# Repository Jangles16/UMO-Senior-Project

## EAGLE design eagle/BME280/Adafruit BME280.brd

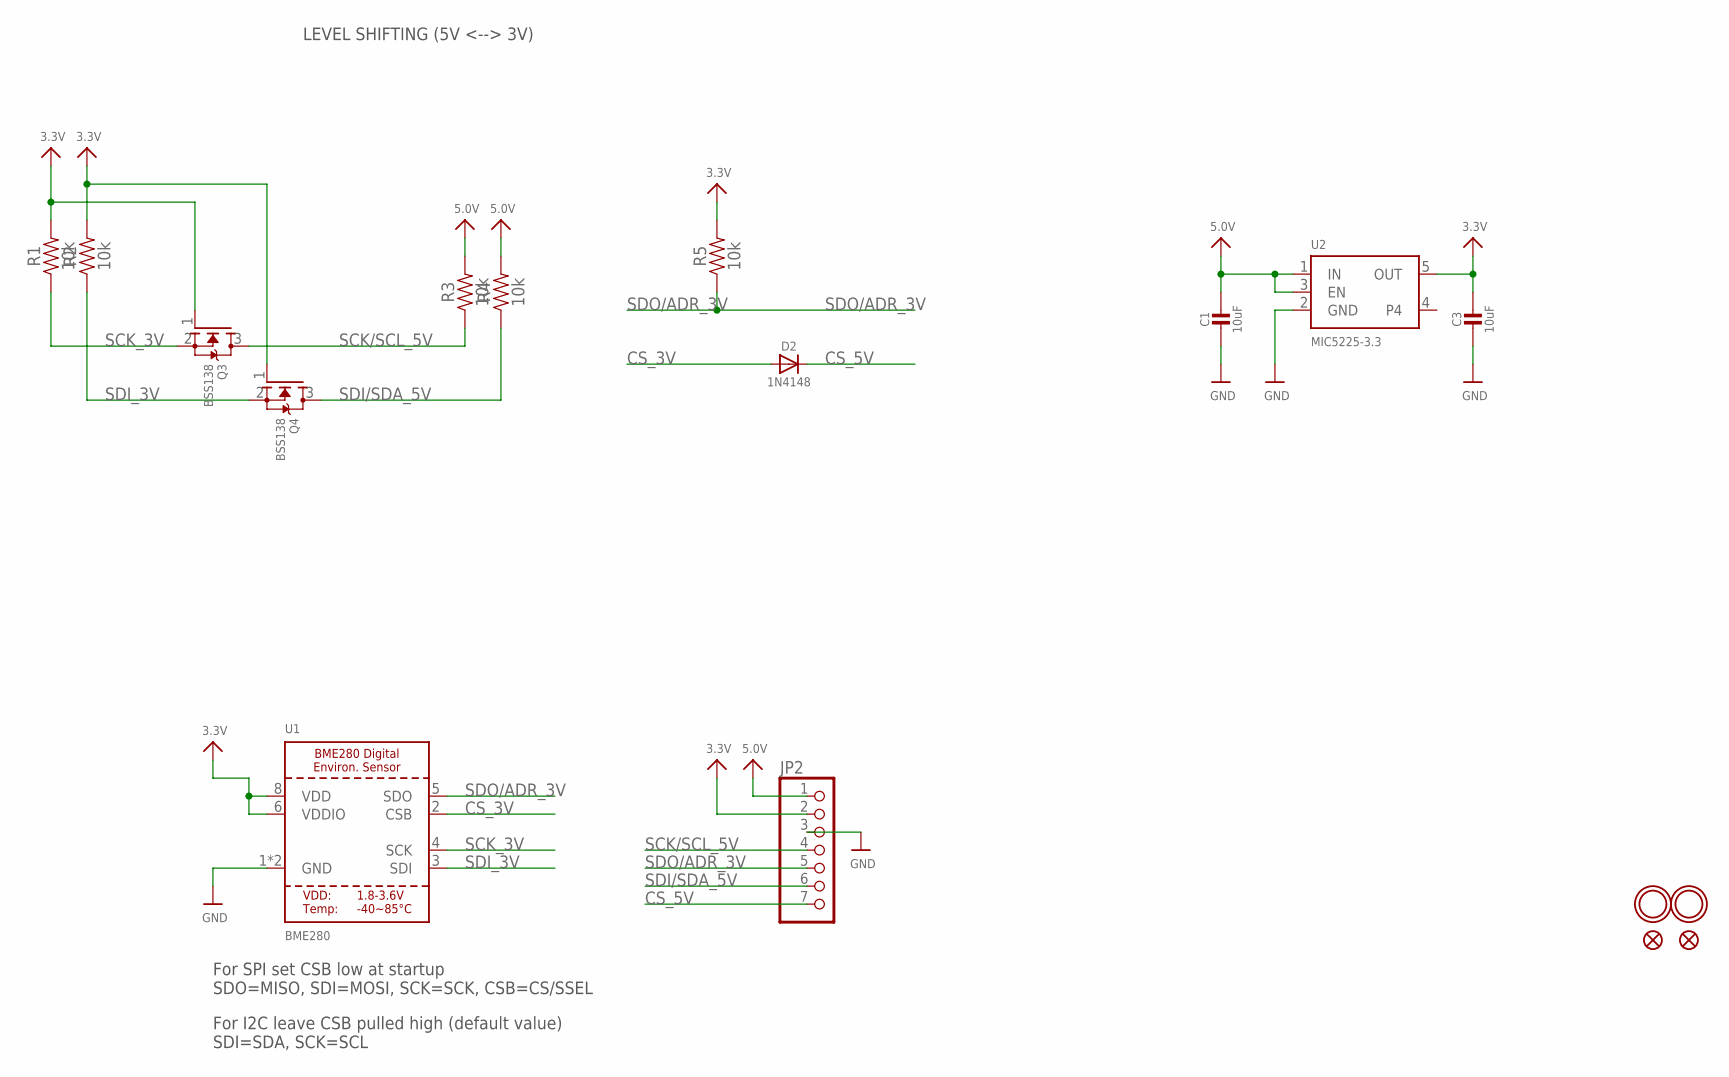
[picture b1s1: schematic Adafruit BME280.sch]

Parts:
C1, C3: 10uF; 0805-NO
D2: 1N4148; SOD-323
JP2: HEADER-1X770MIL; 1X07_ROUND_70
Q3, Q4: BSS138; SOT23-WIDE
R1, R2, R3, R4, R5: 10k; 0603
U1: BME280
U2: MIC5225-3.3; SOT23-5
U$5, U$15: FIDUCIAL""; FIDUCIAL_1MM
U$7, U$8: MOUNTINGHOLE2.0; MOUNTINGHOLE_2.0_PLATED

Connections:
3.3V: C3.1, JP2.2, Q3.1 (G), Q4.1 (G), R1.2, R2.2, R5.2, U1.6 (VDDIO), U1.8 (VDD), U2.5 (OUT)
5.0V: C1.1, JP2.1, R3.2, R4.2, U2.1 (IN), U2.3 (EN)
CS_3V: D2.A, U1.2 (CSB)
CS_5V: D2.C, JP2.7
GND: C1.2, C3.2, JP2.3, U1.1 (GND), U1.7 (GND), U2.2 (GND)
SCK/SCL_5V: JP2.4, Q3.3 (D), R3.1
SCK_3V: Q3.2 (S), R1.1, U1.4 (SCK)
SDI/SDA_5V: JP2.6, Q4.3 (D), R4.1
SDI_3V: Q4.2 (S), R2.1, U1.3 (SDI)
SDO/ADR_3V: JP2.5, R5.1, U1.5 (SDO)

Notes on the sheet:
For SPI set CSB low at startup SDO=MISO, SDI=MOSI, SCK=SCK, CSB=CS/SSEL
For I2C leave CSB pulled high (default value) SDI=SDA, SCK=SCL
LEVEL SHIFTING (5V <--> 3V)

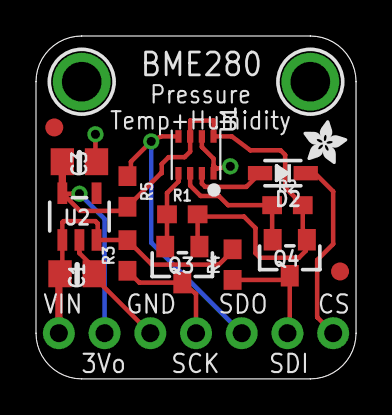
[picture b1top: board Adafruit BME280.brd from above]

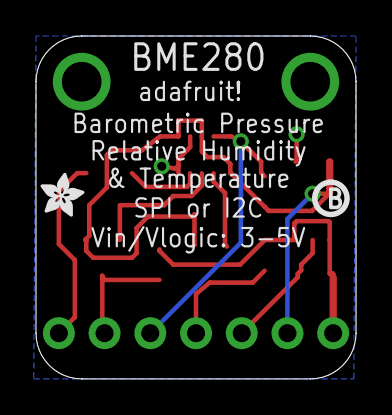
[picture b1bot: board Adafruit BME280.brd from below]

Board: 2 copper layers, 17.8 x 19.1 mm, 20 parts (2 on the bottom side), 10 nets.

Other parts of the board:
U$2, U$6: ADAFRUIT_2.5MM
U$20: PCBFEAT-REV-040

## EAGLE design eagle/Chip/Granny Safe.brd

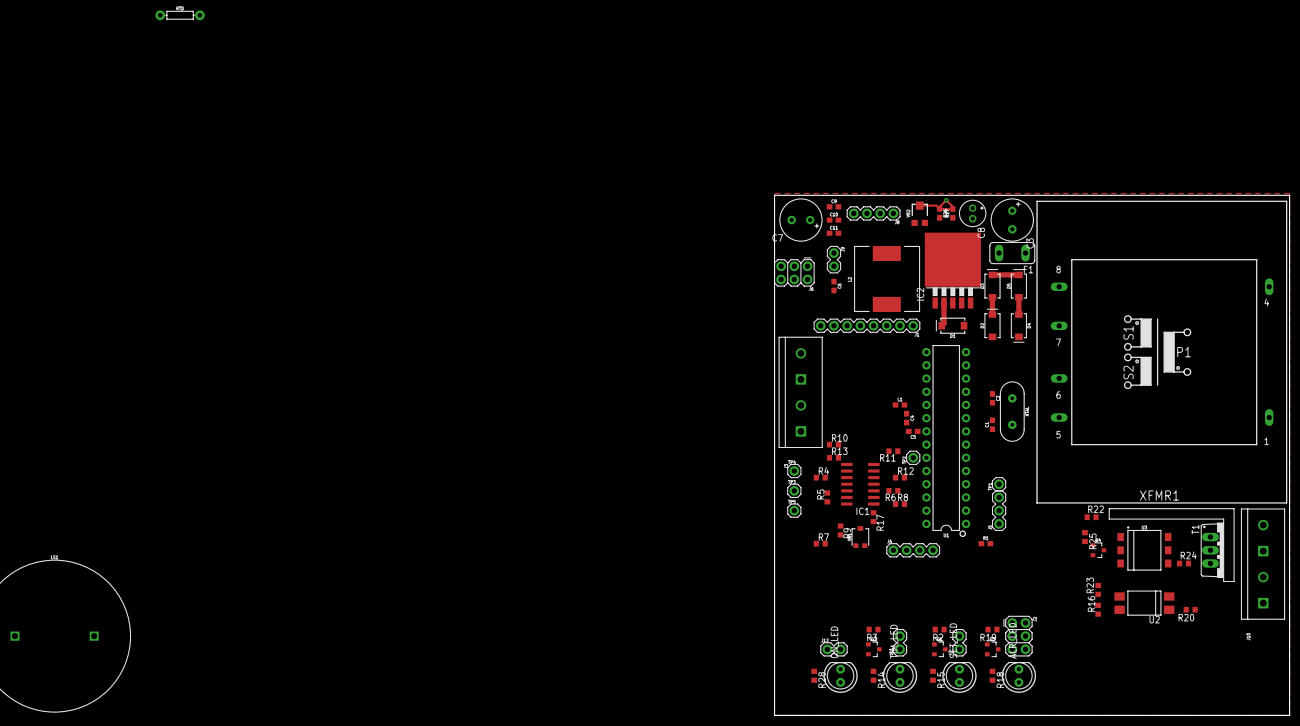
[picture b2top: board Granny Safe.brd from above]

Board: 2 copper layers, 99.0 x 100.0 mm, 87 parts (0 on the bottom side), 59 nets.

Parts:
ALR_LED: LED5MM
C1, C2: 22pF; 0603
C3, C7: 470u; E3,5-8
C4, C5, C6, C9: 0.1uF; 0603
C8: 100u; E2-5
C10: 100pF; 0603
C11: 1nF; 0603
D1, D2, D3, D4, D5: SMA-DIODE
F1: 1.5A; TE5
H1, H2, H3, H4: STAND-OFF
IC1: MCP604SL; SO14
IC2: LM2596S; TO263-5
J1: 3x4 Keypad; 1X08
J2, J6: FEMALE 2x3; 2X3
J3, J10: SCREW-4; SCREWTERMINAL-5MM-2
J4: i2c_16x2; 1X04
J5: 1X03
J7, J11, J12: 1X02
J8: RES JUMPER; 1X04
J9: CKT PWR CONN; 1X02
L1: 10uH; 0603
L2: INDUCTOR; CR75
LS1: SPEAKER; PCB_MOUNT_SPEAKER
ON_LED: LED5MM
Q1, Q2, Q3: SOT23-3
Q4: 2N3904; SOT23-3
R1: 10k; 0603
R2, R3, R19, R25: 2k; R0603
R4, R5: 2.4k; R0603
R6: 100; R0603
R7, R20, R23: 10k; R0603
R8, R9: 20k; R0603
R10, R11: 15k; R0603
R12, R13: 3k; R0603
R14, R15, R18, R28: 150; R0603
R16: 1M; R0603
R17: 5k; R0603
R22: 220; R0603
R24: 180; R0603
R26: 3.3k; 0603
R27: 1k; 0603
RTD: AXIAL-0.3
SET_LED: LED5MM
T1: BT137; TO220BV
TIM_LED: LED5MM
TP1, TP2, TP3, TP4, TP5: 1X01
U1: 328P; DIP28
U2: SFH6206; DIL4-SMD
U3: MOC3051; DIP8SMD
VR1: 10k; TRIMPOT-SMD-3MM-CLOSED
VR2: 10k; TRIMPOT-SMD-TC33X
XFMR1: EE20-2
XTAL: 16MHz; HC49US

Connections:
5V: C6.1, IC1.4, IC1.12, J4.1, J6.1, J6.3, J6.5, J9.2, L1.1, R1.2, R4.2, R5.2, R14.2, R15.2, R18.2, R22.1, R23.2, R28.2, TP4.1, U1.7
ADC0: IC1.7, R11.2, TP2.1, U1.23
ALR: R19.1, U1.18
GATE: R25.1, U1.5
GND: C1.1, C2.1, C3.-, C4.2, C5.2, C6.2, C7.-, C8.-, C9.2, C10.2, C11.2, D1.A, D2.A, D4.C, IC1.11, IC1.13, IC2.3, IC2.5, J3.1, J3.2, J4.2, J6.2, J6.4, J6.6, J8.4, J12.2, ON_LED.K, Q1.2, Q2.2, Q3.2, Q4.2, R6.1, R10.1, R16.1, R27.1, TP3.1, TP5.1, U1.8, U1.22, U2.3, VR2.3
LINE: J10.4, R20.1, T1.T2, U3.6, XFMR1.1
unnamed: C1.2, U1.9, XTAL.2
unnamed: C2.2, U1.10, XTAL.1
unnamed: J1.7, U1.17
unnamed: C5.1, U1.21
unnamed: J1.6, U1.16
unnamed: J1.5, U1.15
unnamed: J1.4, U1.14
unnamed: J1.3, U1.13
unnamed: J1.2, U1.12
unnamed: J1.1, U1.11
unnamed: Q1.1, R2.2
unnamed: IC1.10, J3.3, J3.4, R4.1
unnamed: Q2.1, R3.2
unnamed: IC1.3, R5.1, R6.2
unnamed: IC1.1, R8.2, R12.1
unnamed: J7.1, R15.1, SET_LED.A
unnamed: J11.1, R14.1, TIM_LED.A
unnamed: J11.2, Q2.3, TIM_LED.K
unnamed: J7.2, Q1.3, SET_LED.K
unnamed: R17.2, VR1.2, VR1.3
unnamed: D2.C, D3.A, F1.2
unnamed: ALR_LED.K, J2.1, J2.3, J2.5, Q3.3
unnamed: IC1.2, R7.2, R8.1, R17.1
unnamed: IC1.8, R9.1, R13.1
unnamed: IC1.9, R7.1, R9.2, VR1.1
unnamed: IC1.5, R10.2, R13.2
unnamed: IC1.6, R11.1, R12.2
unnamed: R20.2, U2.1
unnamed: R24.2, T1.G
unnamed: R22.2, U3.1
unnamed: R24.1, U3.4
unnamed: IC2.4, R26.1, R27.2, VR2.2
unnamed: Q4.3, U3.2
unnamed: Q4.1, R25.2
unnamed: J12.1, ON_LED.A, R28.1
unnamed: F1.1, XFMR1.5, XFMR1.7
unnamed: C7.+, C9.1, C10.1, C11.1, J8.1, J9.1, L2.P$2, R26.2, VR2.1
unnamed: ALR_LED.A, J2.2, J2.4, J2.6, R18.1
unnamed: Q3.1, R19.2
unnamed: D4.A, D5.A, XFMR1.6, XFMR1.8
unnamed: C4.1, L1.2, U1.20
unnamed: D1.C, IC2.2, L2.P$1
unnamed: C3.+, C8.+, D3.C, D5.C, IC2.1
NEUT: J10.2, J10.3, U2.2, XFMR1.4
PWR: J10.1, T1.T1
RST: J5.1, R1.1, U1.1
RX: J5.2, U1.2
SCL: J4.4, U1.28
SDA: J4.3, U1.27
SET: R2.1, U1.19
TX: J5.3, U1.3
T_EN: R3.1, U1.6
ZERO: R16.2, R23.1, TP1.1, U1.4, U2.4

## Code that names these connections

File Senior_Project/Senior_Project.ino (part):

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
#define ALARM_PIN     12    //pin 18 on chip, used to control alarm speaker and led
#define SETPOINT_PIN  13    //pin 19 on chip, used control setpoint led
#define ZERO_SENSE    2     //pin 4 on chip, used as external interrupt pin to capture zero crossing event
#define GATE_PIN      3     //pin 5 on chip, used to control the triggering of the triac (pretty sure want PWM here, so chose PWM PIN)
#define HOT_LED_PIN   4     //probably need to change pin (6 on chip currently)
#define KP            2     // PID proportional factor
#define KI            5    // PID integral factor
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
  pinMode(ALARM_PIN, OUTPUT);         //controls alarm speaker and led bjt
  pinMode(SETPOINT_PIN, OUTPUT);      // enables setpoint entered led
  pinMode(ZERO_SENSE, INPUT);         // reads the zero sense signal
  pinMode(GATE_PIN, OUTPUT);          //controls triac gate pin
  pinMode(HOT_LED_PIN, OUTPUT);       //used to control led to signal >120F

  // set up Timer1 
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void zero_crossing() {
  if (zero_state) { //zero sense enabled and hotplate not in full off condition  
    TCCR1B=0x04;                  //start timer 1 with divide by 256 input
    TCNT1 = 0;                    //reset timer 1 - count from zero
  }   
}

ISR(TIMER1_COMPA_vect){                 //comparator match interrupt
  if (zero_state) {                     //zero sense is enable
    digitalWrite(GATE_PIN, HIGH);       //set TRIAC gate to high
    TCNT1 = 65536 + (-498 + OCR1A);      //trigger pulse width, will be full half wave - delay
  }                                     //bigger than 500 and starts skipping some half waves
                                        //given the rise/fall of zero-cross, 500 ~ half wave
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
ISR(TIMER1_OVF_vect){                   //timer 1 overflow interrupt
  if (zero_state) {                     //zero sense is enable
    digitalWrite(GATE_PIN,LOW);         //turn off TRIAC gate
    TCCR1B = 0x00;                      //disable timer, stop unintended triggers
  }
}
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  }
  else {                    //if no setpoint keep hotplate off and disregard zero sense
    zero_state = false;           
    digitalWrite(GATE_PIN,LOW);
  }
}

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
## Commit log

2017-10-29 New Diagram
    Added new software block diagram and removed old ones
2017-10-29 added readme
2017-10-29 Update Diagrams
2017-10-29 added speaker to eagle
2017-10-29 Created custom XFMR in eagle
2017-10-30 Changed schematics and block diagram
2017-10-30 added gifs for presentation
2017-10-30 Moved things around
2017-11-11 added new arduino project
    will end up being the final code
2017-11-12 tweaked code and updated eagle sch
2017-11-13 updated eagle schematic
2017-11-14 Worked on code, added timer stuff
2017-11-14 tiny change
2017-11-15 I think everything is working together
    Will still need to tweak temp sense, PID, and other stuff possibly.
2017-11-16 edited temperature equation variables
2017-11-18 update power supply sch.
    still need to change the inductor footprint
2017-11-18 Think power supply schematic is ready to go.
    Need to decide about XFMR on board or not.
2017-11-18 Updated uc schematic
    dont forget to think about test points
2017-11-18 PWR SUP, all but test point
    need a way to hook up the resistor too
2017-11-18 More updates to schematics
2017-11-18 Put both schematics together
2017-11-19 combined schematic should be all done
2017-11-19 started working on board layout
2017-11-20 Updated board
2017-11-21 worked on board some more
2017-11-21 Worked on the board some more
2017-11-21 more board stuff
2017-11-22 worked on the board some more
    should be pretty close to being done
2017-11-28 worked on board, should be all done
2017-12-13 fixed keypad
2018-03-28 new stuff
2018-03-31 but pres/report stuff in report folder
2018-05-08 Final Report uploaded

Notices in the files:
parts and their libraries:
SparkFun-Resistors: Licensing: Creative Commons ShareAlike 4.0 International - https://creativecommons.org/licenses/by-sa/4.0
